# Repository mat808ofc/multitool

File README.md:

# Mateus's multitool

### Inspiration

I have always loved electronics, physics and engineering and i saw this as an opportunity to see what actually making a dedicated project was like. Next year I will enter a project by ESA called CanSat (i have to build a satellite the size of a can of soda) and i plan on using my multitool to control and get data from the CanSat. I also plan on exploring the firmware and costumize the multitool every once in a while to do something different with it.

### Challenges

My biggest challenge was creating the 3x3 matrix and replacing the top left key with the rotatary encoder switch, but the whole project was very fun to do and the slack community was very helpful (shoutout). Believe it or not, i spent over 12 hours on this project because it was my first and i had to learn how to do things. I think it turned out pretty nice for a first project honestly and i love that now i know all this stuff about electronics! IT'S JUST THE BEGGINING I AM COMING BACK FOR MORE!!

### Extras

I used KiCad to build the PCB, Fusion 360 for the case and QMK as the firmware. In the future, I want to add more components and I WILL ADD MORE COMPONENTS but for now that's it lol.
Honestly i want to add something more here but I don't know what to add..
I'm from Portugal lol

### Specifications

BOM: 
- 8x Cherry MX Switches
- 4x SK6812 MINI-E Leds
- 1x XIAO RP2040
- 8x Blank DSA Keycaps
- 9x through-hole 1N4148 Diodes
- 1x EC11 Rotary encoder
- 1x 0.91 inch OLED display 

Others:
- QMK Firmware
- Top.step
- Bottom.step

### Note:

It doesn't look like it in the case pictures, but it does have space for the PCB and the holes in between keys are for the diodes and not put too much pressure on them.

Schematic            |  PCB         |   Case
:-------------------------:|:-------------------------:|:-------------------------:|
  |   |

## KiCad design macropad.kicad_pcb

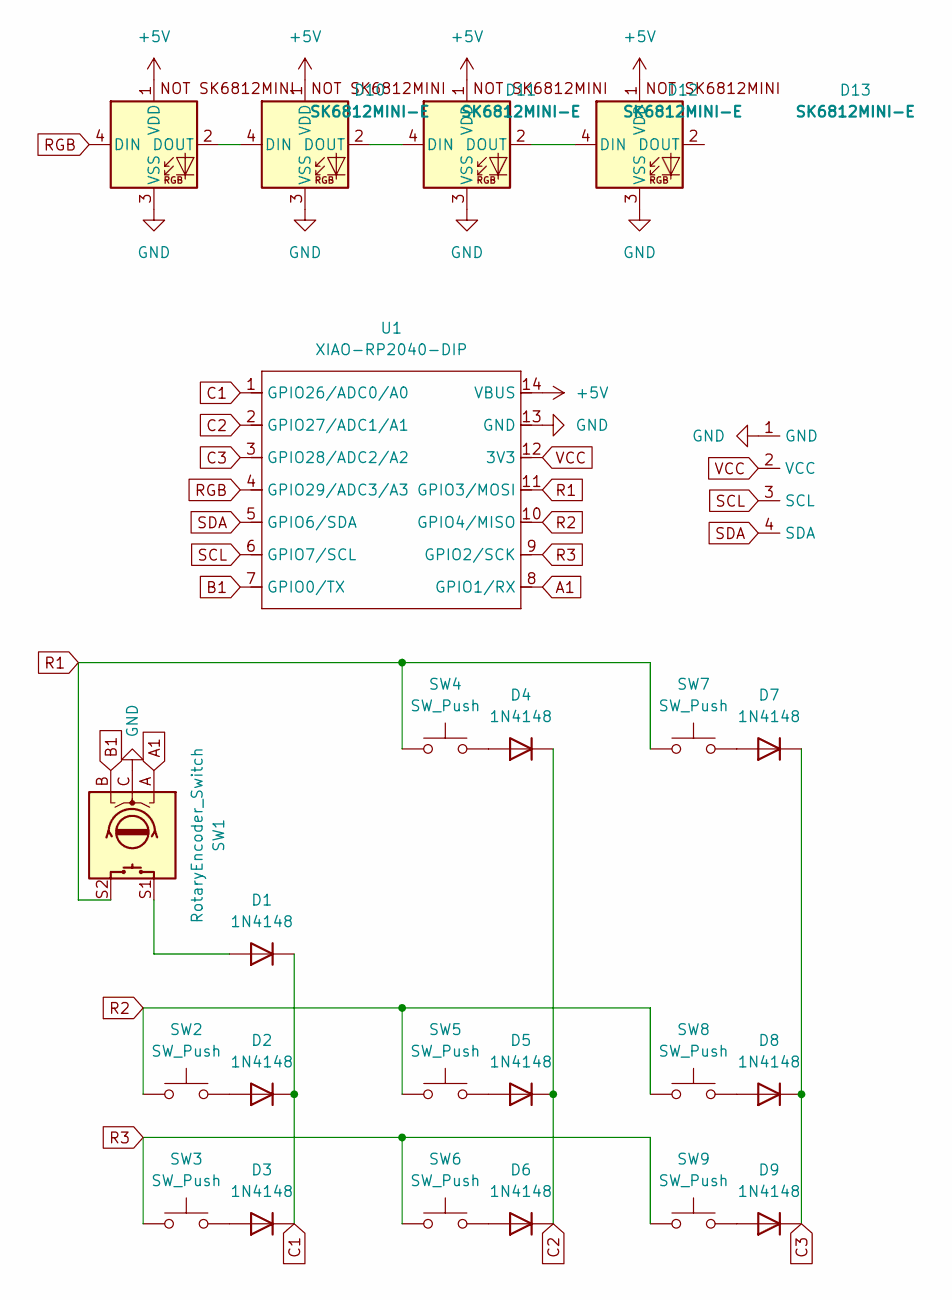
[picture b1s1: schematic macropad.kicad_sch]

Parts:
D1, D2, D3, D4, D5, D6, D7, D8, D9: 1N4148; D_DO-35_SOD27_P7.62mm_Horizontal
D10, D11, D12, D13: SK6812MINI-E; SK6812MINI-E_fixed
SW1: RotaryEncoder_Switch; RotaryEncoder_Alps_EC11E-Switch_Vertical_H20mm
SW2, SW3, SW4, SW5, SW6, SW7, SW8, SW9: SW_Push; SW_Cherry_MX_1.00u_PCB
U1: XIAO-RP2040-DIP
U2: SSD1306-0.91-OLED-4pin-128x32

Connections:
+5V: D10.1 (VDD), D11.1 (VDD), D12.1 (VDD), D13.1 (VDD), U1.14 (VBUS)
A1: SW1.A, U1.8 (GPIO1/RX)
B1: SW1.B, U1.7 (GPIO0/TX)
C1: D1.1 (K), D2.1 (K), D3.1 (K), U1.1 (GPIO26/ADC0/A0)
C2: D4.1 (K), D5.1 (K), D6.1 (K), U1.2 (GPIO27/ADC1/A1)
C3: D7.1 (K), D8.1 (K), D9.1 (K), U1.3 (GPIO28/ADC2/A2)
GND: D10.3 (VSS), D11.3 (VSS), D12.3 (VSS), D13.3 (VSS), SW1.C, U1.13 (GND), U2.1 (GND)
unnamed: D1.2 (A), SW1.S1
unnamed: D2.2 (A), SW2.2
unnamed: D3.2 (A), SW3.2
unnamed: D4.2 (A), SW4.2
unnamed: D5.2 (A), SW5.2
unnamed: D6.2 (A), SW6.2
unnamed: D7.2 (A), SW7.2
unnamed: D8.2 (A), SW8.2
unnamed: D9.2 (A), SW9.2
unnamed: D10.2 (DOUT), D11.4 (DIN)
unnamed: D11.2 (DOUT), D12.4 (DIN)
unnamed: D12.2 (DOUT), D13.4 (DIN)
R1: SW1.S2, SW4.1, SW7.1, U1.11 (GPIO3/MOSI)
R2: SW2.1, SW5.1, SW8.1, U1.10 (GPIO4/MISO)
R3: SW3.1, SW6.1, SW9.1, U1.9 (GPIO2/SCK)
RGB: D10.4 (DIN), U1.4 (GPIO29/ADC3/A3)
SCL: U1.6 (GPIO7/SCL), U2.3 (SCL)
SDA: U1.5 (GPIO6/SDA), U2.4 (SDA)
VCC: U1.12 (3V3), U2.2 (VCC)

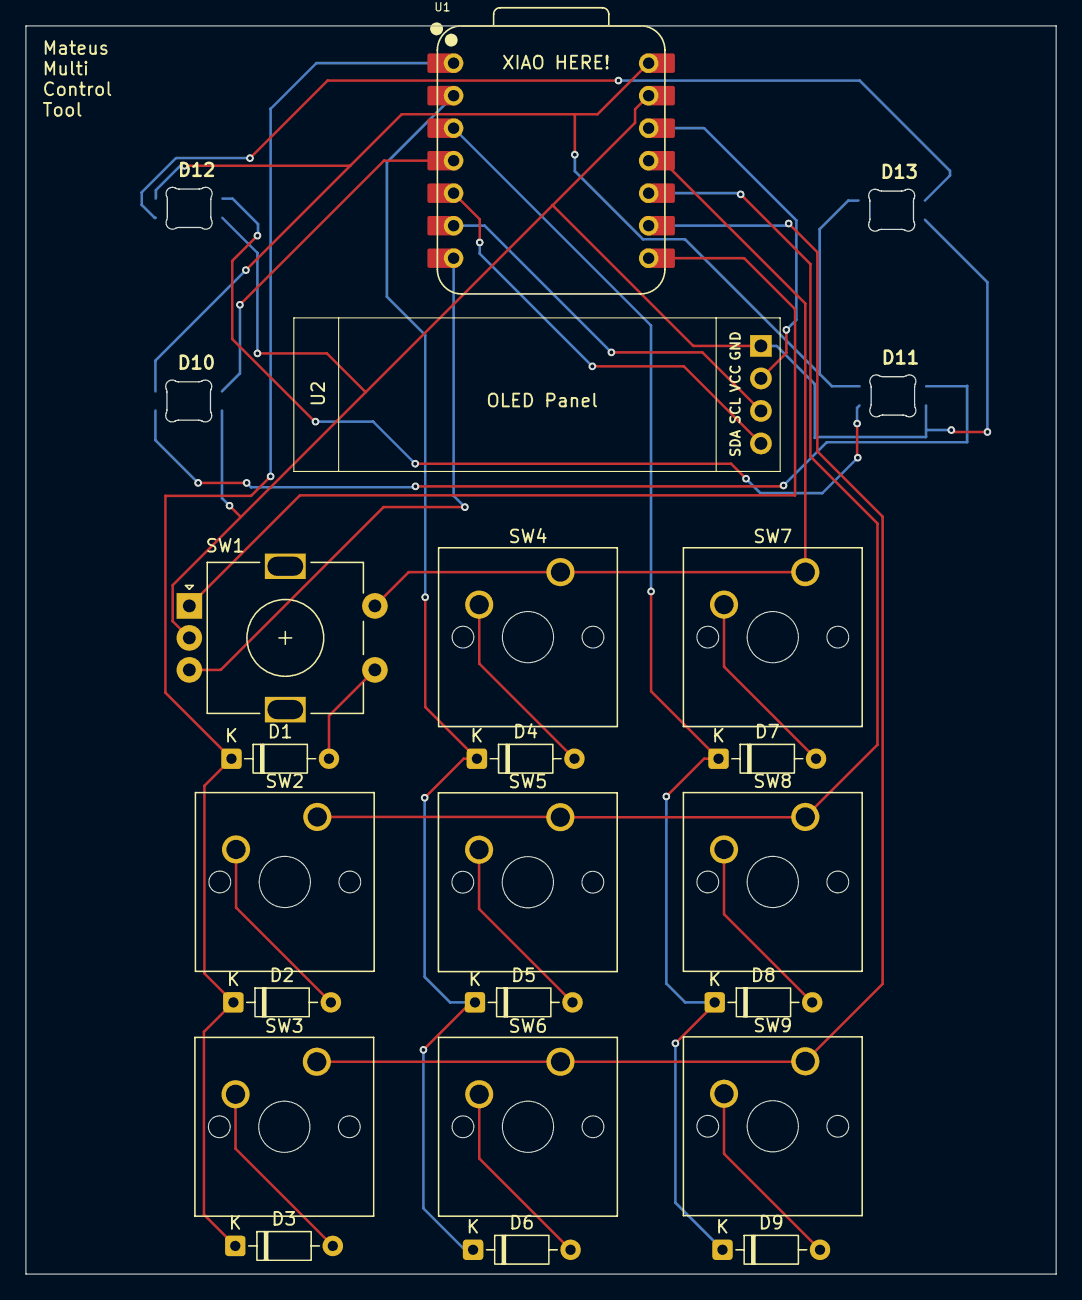
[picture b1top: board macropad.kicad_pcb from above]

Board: 2 copper layers, 80.4 x 97.5 mm, 24 parts (0 on the bottom side), 26 nets.

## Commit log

2026-02-15 Update README with project information and images
    Expanded project details including inspiration, challenges, and specifications.
2026-02-16 Update README with extras and personal notes
    Added extras section detailing tools used and future plans.
2026-02-16 small update
    lol
2026-02-16 Improve clarity in README inspiration section
    Revised text for clarity and conciseness in the inspiration section.
2026-02-16 Update README with new images and PCB note
    Added additional images and a note about PCB space.
2026-02-16 Add updated production
2026-02-16 Added clean project files
